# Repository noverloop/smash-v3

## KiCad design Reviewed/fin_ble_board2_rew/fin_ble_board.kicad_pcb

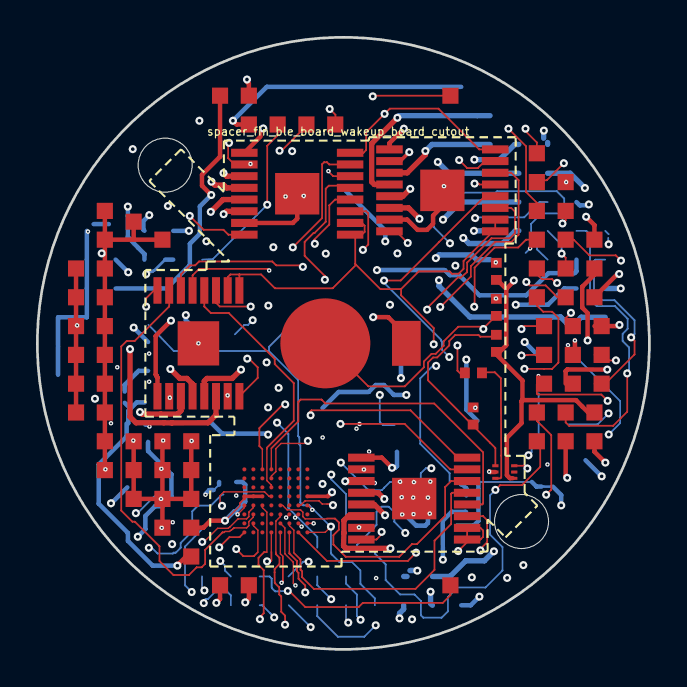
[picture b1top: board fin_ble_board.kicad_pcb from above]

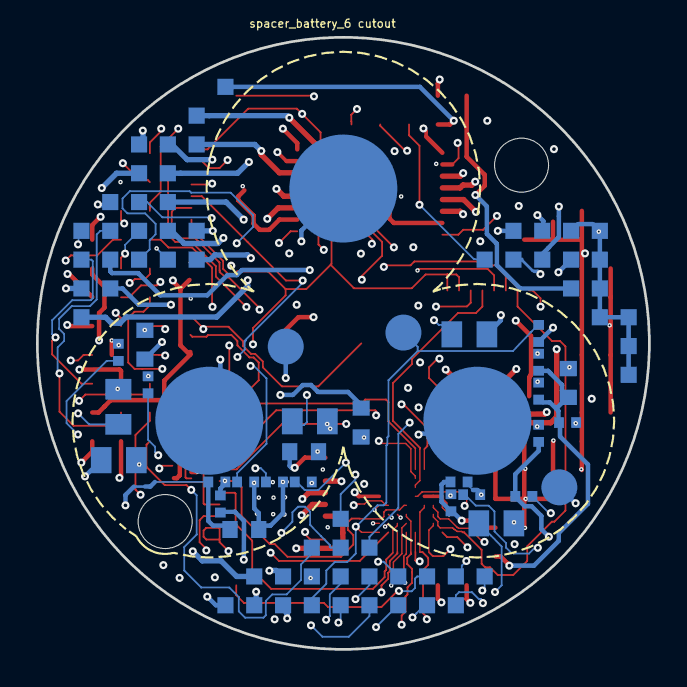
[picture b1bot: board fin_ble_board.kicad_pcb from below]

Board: 14 copper layers, 34.0 x 34.0 mm, 44 parts (31 on the bottom side), 81 nets.

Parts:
C_COMP_PZ: C0402 X7R 100nF; Capacitor_SMD_C_0402_1005Metric
C_FIN1_DVDD, C_FIN2_DVDD, C_FIN3_DVDD, C_FIN4_DVDD: C-Series MIL-PRF-32535 X7R 0805 1uF; Capacitor_SMD_C_0805_2012Metric
C_FIN1_VM, C_FIN2_VM, C_FIN3_VM, C_FIN4_VM: C0402 X7R 100nF; Capacitor_SMD_C_0402_1005Metric
C_FIN_VM_BULK_1, C_FIN_VM_BULK_2, C_FIN_VM_BULK_3, C_FIN_VM_BULK_4, C_FIN_VM_BULK_5: C-Series MIL-PRF-32535 X7R 0603 2.2uF; Capacitor_SMD_C_0603_1608Metric
C_FIN_VREF: C0402 X7R 100nF; Capacitor_SMD_C_0402_1005Metric
C_G0B1_FIN_BULK: C-Series MIL-PRF-32535 X7R 0805 1uF; Capacitor_SMD_C_0805_2012Metric
C_G0B1_FIN_NRST, C_G0B1_FIN_VDD1, C_G0B1_FIN_VDD2, C_G0B1_FIN_VREF: C0402 X7R 100nF; Capacitor_SMD_C_0402_1005Metric
C_J_HALL_FIN_VCC: C0402 X7R 100nF; Capacitor_SMD_C_0402_1005Metric
J_HALL_FIN_GND: J_HALL_FIN_GND; Pogo_Pad_D2.0mm
J_HALL_FIN_OUT: J_HALL_FIN_OUT; Pogo_Pad_D2.0mm
J_HALL_FIN_VCC: J_HALL_FIN_VCC; Pogo_Pad_D2.0mm
J_fin_ble_board_spacer_fin_ble_board_wakeup_board: LGA_lands; J_fin_ble_board_spacer_fin_ble_board_wakeup_board
P_CELL_CONTACTS: BatteryContacts_3
P_PIEZO: SMD10T04R111; PiezoDisc_SMD10T04R111
P_fin_ble_board_spacer_battery_6: LGA_lands; P_fin_ble_board_spacer_battery_6
R_COMP_SER: CRCW0402 100k 1% e3; Resistor_SMD_R_0402_1005Metric
R_FIN1_DECAY, R_FIN2_DECAY, R_FIN3_DECAY, R_FIN4_DECAY: CRCW0402 44.2k 1% e3; Resistor_SMD_R_0402_1005Metric
R_G0B1_FIN_NRST: CRCW0402 10k 1% e3; Resistor_SMD_R_0402_1005Metric
R_J_HALL_FIN_PU: CRCW0402 10k 1% e3; Resistor_SMD_R_0402_1005Metric
R_PIEZO_BLEED: CRCW0402 1M 1% e3; Resistor_SMD_R_0402_1005Metric
R_THR1: CRCW0402 1M 1% e3; Resistor_SMD_R_0402_1005Metric
R_THR2: CRCW0402 100k 1% e3; Resistor_SMD_R_0402_1005Metric
U_COMP_PZ: TLV3691IDPFR; DPF0006A
U_FIN1, U_FIN2, U_FIN3, U_FIN4: DRV8428EPWPR; SOP65P640X120-17N
U_G0B1_FIN: STM32G0B1REI6N; BGA64C50P8X8_500X500X60

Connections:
3V3: C_G0B1_FIN_BULK.1, C_G0B1_FIN_VDD1.1, C_G0B1_FIN_VDD2.1, C_G0B1_FIN_VREF.1, C_J_HALL_FIN_VCC.1, J_HALL_FIN_VCC.1, J_fin_ble_board_spacer_fin_ble_board_wa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.1, J_fin_ble_board_spacer_fin_ble_board_wa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.35, J_fin_ble_board_spacer_fin_ble_board_wa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.41, P_fin_ble_board_spacer_battery_6.23, P_fin_ble_board_spacer_battery_6.47, P_fin_ble_board_spacer_battery_6.52, R_G0B1_FIN_NRST.1, R_J_HALL_FIN_PU.1, U_G0B1_FIN.D1, U_G0B1_FIN.D2, U_G0B1_FIN.D3, U_G0B1_FIN.D8
3V3_AON: C_COMP_PZ.1, J_fin_ble_board_spacer_fin_ble_board_wa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.2, J_fin_ble_board_spacer_fin_ble_board_wa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.36, P_fin_ble_board_spacer_battery_6.24, P_fin_ble_board_spacer_battery_6.48, R_THR1.1, U_COMP_PZ.6
ACTIVATE_CONFIRM: J_fin_ble_board_spacer_fin_ble_board_wa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.3, P_fin_ble_board_spacer_battery_6.3
ACTIVATE_SET: J_fin_ble_board_spacer_fin_ble_board_wa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.4, P_fin_ble_board_spacer_battery_6.4
BAT_CELL1_POS: J_fin_ble_board_spacer_fin_ble_board_wa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.5, P_CELL_CONTACTS.1
BAT_CELL2_POS: J_fin_ble_board_spacer_fin_ble_board_wa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.6, P_CELL_CONTACTS.2
BAT_CELL3_POS: J_fin_ble_board_spacer_fin_ble_board_wa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.7, P_CELL_CONTACTS.3
BAT_PROT: J_fin_ble_board_spacer_fin_ble_board_wa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.8, J_fin_ble_board_spacer_fin_ble_board_wa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.37, P_fin_ble_board_spacer_battery_6.5, P_fin_ble_board_spacer_battery_6.49
BAT_RAW: J_fin_ble_board_spacer_fin_ble_board_wa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.9, J_fin_ble_board_spacer_fin_ble_board_wa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.38, P_fin_ble_board_spacer_battery_6.6, P_fin_ble_board_spacer_battery_6.50
BOOT0: J_fin_ble_board_spacer_fin_ble_board_wa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.10, P_fin_ble_board_spacer_battery_6.7
COMP_5V: J_fin_ble_board_spacer_fin_ble_board_wa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.11, J_fin_ble_board_spacer_fin_ble_board_wa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.39, P_fin_ble_board_spacer_battery_6.8, P_fin_ble_board_spacer_battery_6.51
COMP_5V_RAW: C_FIN1_VM.1, C_FIN2_VM.1, C_FIN3_VM.1, C_FIN4_VM.1, C_FIN_VM_BULK_1.1, C_FIN_VM_BULK_2.1, C_FIN_VM_BULK_3.1, C_FIN_VM_BULK_4.1, C_FIN_VM_BULK_5.1, J_fin_ble_board_spacer_fin_ble_board_wa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.12, J_fin_ble_board_spacer_fin_ble_board_wa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.40, U_FIN1.1, U_FIN2.1, U_FIN3.1, U_FIN4.1
COMP_INM: R_THR1.2, R_THR2.1, U_COMP_PZ.3
COMP_INP: R_COMP_SER.2, U_COMP_PZ.1
COMP_OUT: J_fin_ble_board_spacer_fin_ble_board_wa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.13, U_COMP_PZ.4
COMP_SWDCLK: J_fin_ble_board_spacer_fin_ble_board_wa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.14, P_fin_ble_board_spacer_battery_6.9
COMP_SWDIO: J_fin_ble_board_spacer_fin_ble_board_wa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.15, P_fin_ble_board_spacer_battery_6.10
EXT_CAN_RX: J_fin_ble_board_spacer_fin_ble_board_wa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.16, P_fin_ble_board_spacer_battery_6.11
EXT_CAN_TX: J_fin_ble_board_spacer_fin_ble_board_wa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.17, P_fin_ble_board_spacer_battery_6.14
FIN1_AEN: U_FIN1.15, U_G0B1_FIN.E3
FIN1_AOUT1: P_fin_ble_board_spacer_battery_6.13, U_FIN1.3
FIN1_AOUT2: P_fin_ble_board_spacer_battery_6.12, U_FIN1.4
FIN1_APH: U_FIN1.14, U_G0B1_FIN.H5
FIN1_BEN: U_FIN1.13, U_G0B1_FIN.F5
FIN1_BOUT1: P_fin_ble_board_spacer_battery_6.15, U_FIN1.6
FIN1_BOUT2: P_fin_ble_board_spacer_battery_6.16, U_FIN1.5
FIN1_BPH: U_FIN1.12, U_G0B1_FIN.B4
FIN1_DECAY: R_FIN1_DECAY.1, U_FIN1.11
FIN1_DVDD: C_FIN1_DVDD.1, U_FIN1.8
FIN2_AEN: U_FIN2.15, U_G0B1_FIN.F2
FIN2_AOUT1: P_fin_ble_board_spacer_battery_6.17, U_FIN2.3
FIN2_AOUT2: P_fin_ble_board_spacer_battery_6.18, U_FIN2.4
FIN2_APH: U_FIN2.14, U_G0B1_FIN.H6
FIN2_BEN: U_FIN2.13, U_G0B1_FIN.G5
FIN2_BOUT1: P_fin_ble_board_spacer_battery_6.19, U_FIN2.6
FIN2_BOUT2: P_fin_ble_board_spacer_battery_6.20, U_FIN2.5
FIN2_BPH: U_FIN2.12, U_G0B1_FIN.C4
FIN2_DECAY: R_FIN2_DECAY.1, U_FIN2.11
FIN2_DVDD: C_FIN2_DVDD.1, U_FIN2.8
FIN3_AEN: U_FIN3.15, U_G0B1_FIN.G2
FIN3_AOUT1: P_fin_ble_board_spacer_battery_6.21, U_FIN3.3
FIN3_AOUT2: P_fin_ble_board_spacer_battery_6.22, U_FIN3.4
FIN3_APH: U_FIN3.14, U_G0B1_FIN.E7
FIN3_BEN: U_FIN3.13, U_G0B1_FIN.H7
FIN3_BOUT1: P_fin_ble_board_spacer_battery_6.1, U_FIN3.6
FIN3_BOUT2: P_fin_ble_board_spacer_battery_6.2, U_FIN3.5
FIN3_BPH: U_FIN3.12, U_G0B1_FIN.D4
FIN3_DECAY: R_FIN3_DECAY.1, U_FIN3.11
FIN3_DVDD: C_FIN3_DVDD.1, U_FIN3.8
FIN4_AEN: U_FIN4.15, U_G0B1_FIN.H1
FIN4_AOUT1: P_fin_ble_board_spacer_battery_6.25, U_FIN4.3
FIN4_AOUT2: P_fin_ble_board_spacer_battery_6.26, U_FIN4.4
FIN4_APH: U_FIN4.14, U_G0B1_FIN.E5
FIN4_BEN: U_FIN4.13, U_G0B1_FIN.G6
FIN4_BOUT1: P_fin_ble_board_spacer_battery_6.27, U_FIN4.6
FIN4_BOUT2: P_fin_ble_board_spacer_battery_6.28, U_FIN4.5
FIN4_BPH: U_FIN4.12, U_G0B1_FIN.A4
FIN4_DECAY: R_FIN4_DECAY.1, U_FIN4.11
FIN4_DVDD: C_FIN4_DVDD.1, U_FIN4.8
FIN_HALL: J_HALL_FIN_OUT.1, P_fin_ble_board_spacer_battery_6.29, R_J_HALL_FIN_PU.2, U_G0B1_FIN.H8
FIN_NSLEEP: U_FIN1.16, U_FIN2.16, U_FIN3.16, U_FIN4.16, U_G0B1_FIN.A3
FIN_VREF: C_FIN_VREF.1, U_FIN1.9, U_FIN1.10, U_FIN2.9, U_FIN2.10, U_FIN3.9, U_FIN3.10, U_FIN4.9, U_FIN4.10, U_G0B1_FIN.H4
FLEX_GND: C_COMP_PZ.2, C_FIN1_DVDD.2, C_FIN1_VM.2, C_FIN2_DVDD.2, C_FIN2_VM.2, C_FIN3_DVDD.2, C_FIN3_VM.2, C_FIN4_DVDD.2, C_FIN4_VM.2, C_FIN_VM_BULK_1.2, C_FIN_VM_BULK_2.2, C_FIN_VM_BULK_3.2, C_FIN_VM_BULK_4.2, C_FIN_VM_BULK_5.2, C_FIN_VREF.2, C_G0B1_FIN_BULK.2, C_G0B1_FIN_NRST.2, C_G0B1_FIN_VDD1.2, C_G0B1_FIN_VDD2.2, C_G0B1_FIN_VREF.2, C_J_HALL_FIN_VCC.2, J_HALL_FIN_GND.1, J_fin_ble_board_spacer_fin_ble_board_wa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.18, J_fin_ble_board_spacer_fin_ble_board_wa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.42, J_fin_ble_board_spacer_fin_ble_board_wa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.43, J_fin_ble_board_spacer_fin_ble_board_wa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.44, J_fin_ble_board_spacer_fin_ble_board_wa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.45, J_fin_ble_board_spacer_fin_ble_board_wa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.46, J_fin_ble_board_spacer_fin_ble_board_wa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.47, J_fin_ble_board_spacer_fin_ble_board_wa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.48, J_fin_ble_board_spacer_fin_ble_board_wa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.49, J_fin_ble_board_spacer_fin_ble_board_wa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.50, J_fin_ble_board_spacer_fin_ble_board_wa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.51, J_fin_ble_board_spacer_fin_ble_board_wa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.52, J_fin_ble_board_spacer_fin_ble_board_wa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.53, J_fin_ble_board_spacer_fin_ble_board_wa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.54, J_fin_ble_board_spacer_fin_ble_board_wa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.55, J_fin_ble_board_spacer_fin_ble_board_wa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.56, J_fin_ble_board_spacer_fin_ble_board_wa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.57, J_fin_ble_board_spacer_fin_ble_board_wa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.58, J_fin_ble_board_spacer_fin_ble_board_wa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.59, J_fin_ble_board_spacer_fin_ble_board_wa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.60, J_fin_ble_board_spacer_fin_ble_board_wa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.61, J_fin_ble_board_spacer_fin_ble_board_wa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.62, J_fin_ble_board_spacer_fin_ble_board_wa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.63, J_fin_ble_board_spacer_fin_ble_board_wa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.64, J_fin_ble_board_spacer_fin_ble_board_wa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.65, J_fin_ble_board_spacer_fin_ble_board_wa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.66, J_fin_ble_board_spacer_fin_ble_board_wa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.67, J_fin_ble_board_spacer_fin_ble_board_wa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.68, J_fin_ble_board_spacer_fin_ble_board_wa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.69, P_PIEZO.2, P_fin_ble_board_spacer_battery_6.30, P_fin_ble_board_spacer_battery_6.53, P_fin_ble_board_spacer_battery_6.54, P_fin_ble_board_spacer_battery_6.55, P_fin_ble_board_spacer_battery_6.56, P_fin_ble_board_spacer_battery_6.57, P_fin_ble_board_spacer_battery_6.58, P_fin_ble_board_spacer_battery_6.59, P_fin_ble_board_spacer_battery_6.60, R_FIN1_DECAY.2, R_FIN2_DECAY.2, R_FIN3_DECAY.2, R_FIN4_DECAY.2, R_PIEZO_BLEED.2, R_THR2.2, U_COMP_PZ.2, U_FIN1.2, U_FIN1.7, U_FIN1.17, U_FIN2.2, U_FIN2.7, U_FIN2.17, U_FIN3.2, U_FIN3.7, U_FIN3.17, U_FIN4.2, U_FIN4.7, U_FIN4.17, U_G0B1_FIN.E1, U_G0B1_FIN.E8
G0B1_FIN_NRST: C_G0B1_FIN_NRST.1, R_G0B1_FIN_NRST.2, U_G0B1_FIN.E2
GPIO_EXT_0: J_fin_ble_board_spacer_fin_ble_board_wa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.19, P_fin_ble_board_spacer_battery_6.31
GPIO_EXT_1: J_fin_ble_board_spacer_fin_ble_board_wa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.20, P_fin_ble_board_spacer_battery_6.32
GPIO_EXT_2: J_fin_ble_board_spacer_fin_ble_board_wa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.21, P_fin_ble_board_spacer_battery_6.33
GPIO_EXT_3: J_fin_ble_board_spacer_fin_ble_board_wa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.22, P_fin_ble_board_spacer_battery_6.34
H3LIS_INT1: J_fin_ble_board_spacer_fin_ble_board_wa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.23, P_fin_ble_board_spacer_battery_6.35
I2C3_SCL: J_fin_ble_board_spacer_fin_ble_board_wa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.24, P_fin_ble_board_spacer_battery_6.36
I2C3_SDA: J_fin_ble_board_spacer_fin_ble_board_wa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.25, P_fin_ble_board_spacer_battery_6.37
JUMP_WAKE: J_fin_ble_board_spacer_fin_ble_board_wa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.26, P_fin_ble_board_spacer_battery_6.38
NRST: J_fin_ble_board_spacer_fin_ble_board_wa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.27, P_fin_ble_board_spacer_battery_6.39
PIEZO_P: P_PIEZO.1, R_COMP_SER.1, R_PIEZO_BLEED.1
SWO: J_fin_ble_board_spacer_fin_ble_board_wa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.28, P_fin_ble_board_spacer_battery_6.40
SYS_I2C_SCL: J_fin_ble_board_spacer_fin_ble_board_wa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.29, P_fin_ble_board_spacer_battery_6.41
SYS_I2C_SDA: J_fin_ble_board_spacer_fin_ble_board_wa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.30, P_fin_ble_board_spacer_battery_6.42
SYS_SPI_CS_FIN: J_fin_ble_board_spacer_fin_ble_board_wa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.31, P_fin_ble_board_spacer_battery_6.43, U_G0B1_FIN.G7
SYS_SPI_MISO: J_fin_ble_board_spacer_fin_ble_board_wa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.32, P_fin_ble_board_spacer_battery_6.44, U_G0B1_FIN.F6
SYS_SPI_MOSI: J_fin_ble_board_spacer_fin_ble_board_wa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.33, P_fin_ble_board_spacer_battery_6.45, U_G0B1_FIN.F7
SYS_SPI_SCLK: J_fin_ble_board_spacer_fin_ble_board_wa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.34, P_fin_ble_board_spacer_battery_6.46, U_G0B1_FIN.G8

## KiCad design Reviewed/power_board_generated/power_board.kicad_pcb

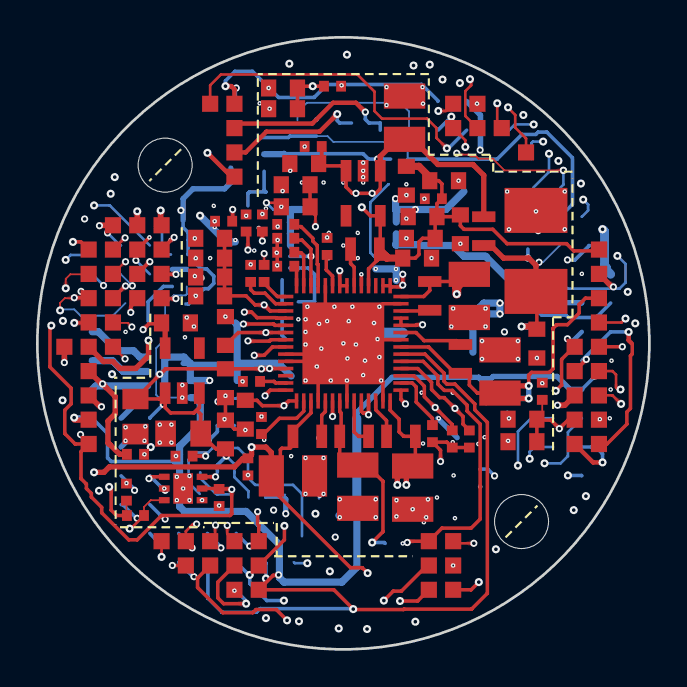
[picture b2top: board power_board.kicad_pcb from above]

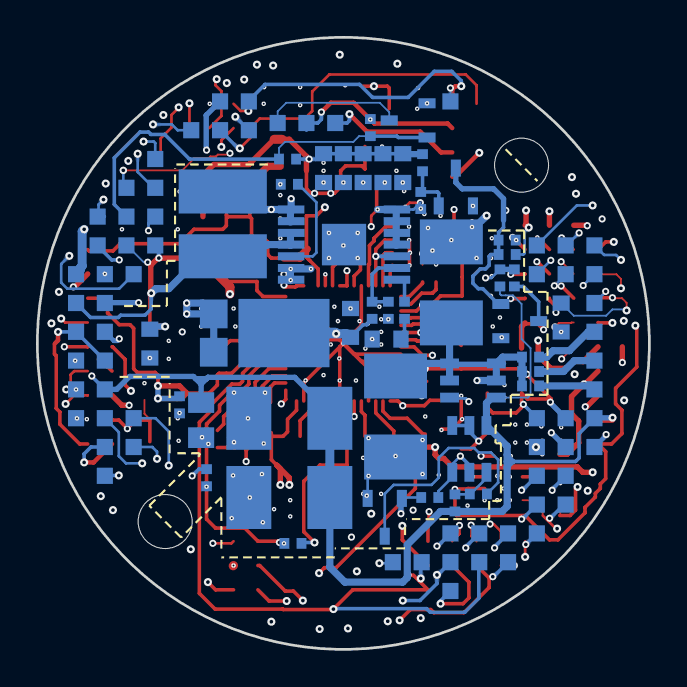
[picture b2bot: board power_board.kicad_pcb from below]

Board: 8 copper layers, 34.0 x 34.0 mm, 114 parts (45 on the bottom side), 98 nets.

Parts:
CBAT1, CBAT2: T528W 100uF (7343-15 thinnest variant); Capacitor_Tantalum_SMD_CP_EIA-7343-15_Kemet-W
CBAT3: C-Series MIL-PRF-32535 X7R 0805 1uF; Capacitor_SMD_C_0805_2012Metric
C_BAT_BULK1, C_BAT_BULK2: T528W 470uF (7343-15 thinnest variant); Capacitor_Tantalum_SMD_CP_EIA-7343-15_Kemet-W
C_BOOST_COMP: C-Series MIL-PRF-32535 X7R 0603 220nF; Capacitor_SMD_C_0603_1608Metric
C_BOOST_OUT1: T528W 47uF (7343-15 thinnest variant); Capacitor_Tantalum_SMD_CP_EIA-7343-15_Kemet-W
C_BOOST_OUT2_1, C_BOOST_OUT2_2, C_BOOST_OUT2_3, C_BOOST_OUT2_4, C_BOOST_OUT2_5: C-Series MIL-PRF-32535 X7R 0603 2.2uF; Capacitor_SMD_C_0603_1608Metric
C_BOOST_OUT3: C0402 X7R 100nF; Capacitor_SMD_C_0402_1005Metric
C_BOOST_SS: C0402 X7R 47nF; Capacitor_SMD_C_0402_1005Metric
C_CAM_LDO_VAA_IN: C-Series MIL-PRF-32535 X7R 0805 1uF; Capacitor_SMD_C_0805_2012Metric
C_CAM_LDO_VAA_OUT_1, C_CAM_LDO_VAA_OUT_2: C-Series MIL-PRF-32535 X7R 0603 2.2uF; Capacitor_SMD_C_0603_1608Metric
C_CAM_LDO_VDD_IN: C-Series MIL-PRF-32535 X7R 0805 1uF; Capacitor_SMD_C_0805_2012Metric
C_CAM_LDO_VDD_OUT: C-Series MIL-PRF-32535 X7R 0603 2.2uF; Capacitor_SMD_C_0603_1608Metric
C_PMIC_0V9_1, C_PMIC_0V82_1, C_PMIC_1V8_1, C_PMIC_3V3_1: T491T 22uF (3528-12 thinnest variant); Capacitor_Tantalum_SMD_CP_EIA-3528-12_Kemet-T
C_PMIC_0V9_2, C_PMIC_0V82_2, C_PMIC_1V2_2, C_PMIC_1V8_2, C_PMIC_2V8_2, C_PMIC_3V3_2: C0402 X7R 100nF; Capacitor_SMD_C_0402_1005Metric
C_PMIC_1V2_1_1, C_PMIC_1V2_1_2, C_PMIC_1V2_1_3, C_PMIC_1V2_1_4, C_PMIC_1V2_1_5, C_PMIC_2V8_1_1, C_PMIC_2V8_1_2, C_PMIC_5V_FILT_1, C_PMIC_5V_FILT_2, C_PMIC_5V_FILT_3, C_PMIC_5V_FILT_4, C_PMIC_5V_FILT_5: C-Series MIL-PRF-32535 X7R 0603 2.2uF; Capacitor_SMD_C_0603_1608Metric
C_PMIC_INTLDO_1, C_PMIC_INTLDO_2: C-Series MIL-PRF-32535 X7R 0603 2.2uF; Capacitor_SMD_C_0603_1608Metric
C_PMIC_LDO1, C_PMIC_LDO2, C_PMIC_LDO4, C_PMIC_LDO6, C_PMIC_LDO7, C_PMIC_LDO8: C0402 X7R 100nF; Capacitor_SMD_C_0402_1005Metric
C_PMIC_VIN1: T491T 22uF (3528-12 thinnest variant); Capacitor_Tantalum_SMD_CP_EIA-3528-12_Kemet-T
C_PMIC_VIN2: C0402 X7R 100nF; Capacitor_SMD_C_0402_1005Metric
C_PMIC_VIN3, C_PMIC_VIN4, C_PMIC_VIN5, C_PMIC_VIN6: C-Series MIL-PRF-32535 X7R 0603 2.2uF; Capacitor_SMD_C_0603_1608Metric
C_PMIC_VLX7: C0402 X7R 100nF; Capacitor_SMD_C_0402_1005Metric
C_PMIC_VOUT7: C0402 X7R 100nF; Capacitor_SMD_C_0402_1005Metric
C_PMIC_VPP_1: T491T 22uF (3528-12 thinnest variant); Capacitor_Tantalum_SMD_CP_EIA-3528-12_Kemet-T
C_PMIC_VPP_2: C0402 X7R 100nF; Capacitor_SMD_C_0402_1005Metric
C_TMP1: C0402 X7R 100nF; Capacitor_SMD_C_0402_1005Metric
C_USB_VBUS_1, C_USB_VBUS_2, C_USB_VBUS_3, C_USB_VBUS_4, C_USB_VBUS_5: C-Series MIL-PRF-32535 X7R 0603 2.2uF; Capacitor_SMD_C_0603_1608Metric
D_BOOST_COMP: PMEG040V050EPE-QZ; PMEG040V050EPEQZ
J_power_board_spacer_power_board_companion_compute: LGA_lands; J_power_board_spacer_power_board_companion_compute
L_BOOST_COMP: 744043100; INDPM4848X280N
L_PMIC_BUCK1, L_PMIC_BUCK5, L_PMIC_BUCK6: TMS201210ALM-1R0MTAA; Inductor_SMD_L_2012_2.0x1.25mm
L_PMIC_BUCK2, L_PMIC_BUCK3, L_PMIC_BUCK4: TMS201210ALM-2R2MTAA; Inductor_SMD_L_2012_2.0x1.25mm
L_PMIC_FILT: TMS201210ALM-1R0MTAA; Inductor_SMD_L_2012_2.0x1.25mm
P_power_board_spacer_wakeup_board_power_board: LGA_lands; P_power_board_spacer_wakeup_board_power_board
Q_ISO: DMP6110SVT-7; SOT95P280X100-6N
Q_ISO_DRV: BSS138LT1G; SOT96P237X111-3N
Q_ISO_USB: BSS138LT1G; SOT96P237X111-3N
Q_USBOR_DRV: BSS138LT1G; SOT96P237X111-3N
Q_USB_OR: DMP6110SVT-7; SOT95P280X100-6N
Q_USB_WAKE: BSS138LT1G; SOT96P237X111-3N
R_BAT1_ISO, R_BAT2_ISO, R_BAT3_ISO: CRCW0402 200m 1% e3; Resistor_SMD_R_0402_1005Metric
R_BOOST_COMP: CRCW0402 1.6k 1% e3; Resistor_SMD_R_0402_1005Metric
R_BOOST_FREQ: CRCW0402 176k 1% e3; Resistor_SMD_R_0402_1005Metric
R_BOOST_R1: CRCW0402 309k 1% e3; Resistor_SMD_R_0402_1005Metric
R_BOOST_R2: CRCW0402 100k 1% e3; Resistor_SMD_R_0402_1005Metric
R_ISO_EN_PD: CRCW0402 100k 1% e3; Resistor_SMD_R_0402_1005Metric
R_ISO_EN_S: CRCW0402 10k 1% e3; Resistor_SMD_R_0402_1005Metric
R_ISO_H: CRCW0402 100k 1% e3; Resistor_SMD_R_0402_1005Metric
R_ISO_L: CRCW0402 10k 1% e3; Resistor_SMD_R_0402_1005Metric
R_ISO_USB_H: CRCW0402 100k 1% e3; Resistor_SMD_R_0402_1005Metric
R_ISO_USB_L: CRCW0402 100k 1% e3; Resistor_SMD_R_0402_1005Metric
R_PMIC_NRST: CRCW0402 10k 1% e3; Resistor_SMD_R_0402_1005Metric
R_PMIC_PONKEY: CRCW0402 10k 1% e3; Resistor_SMD_R_0402_1005Metric
R_PMIC_PWRCTRL1_PD, R_PMIC_PWRCTRL2_PD, R_PMIC_PWRCTRL3_PD: CRCW0402 10k 1% e3; Resistor_SMD_R_0402_1005Metric
R_PMIC_PWR_OK: CRCW0402 10k 1% e3; Resistor_SMD_R_0402_1005Metric
R_PMIC_WAKEUP: CRCW0402 10k 1% e3; Resistor_SMD_R_0402_1005Metric
R_TMP1_ALERT_PU: CRCW0402 10k 1% e3; Resistor_SMD_R_0402_1005Metric
R_USBOR_H: CRCW0402 100k 1% e3; Resistor_SMD_R_0402_1005Metric
R_USBOR_L: CRCW0402 10k 1% e3; Resistor_SMD_R_0402_1005Metric
R_USBOR_USB_H: CRCW0402 100k 1% e3; Resistor_SMD_R_0402_1005Metric
R_USBOR_USB_L: CRCW0402 100k 1% e3; Resistor_SMD_R_0402_1005Metric
R_USBWK_G: CRCW0402 10k 1% e3; Resistor_SMD_R_0402_1005Metric
R_USBWK_PD: CRCW0402 100k 1% e3; Resistor_SMD_R_0402_1005Metric
U_CAM_LDO_VAA: LP5907MFX-2.8/NOPB; SOT95P280X145-5N
U_CAM_LDO_VDD: LP5907MFX-1.2/NOPB; SOT95P280X145-5N
U_COMP_BOOST: TPS61175PWPR; SOP65P640X120-15N
U_PMIC: STPMIC25APQR; QFN40P650X650X90-57N-D
U_TMP1: TMP117MAIDRVR; SON65P200X200X80-7N

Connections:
3V3: C_TMP1.1, J_power_board_spacer_power_board_compan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.1, J_power_board_spacer_power_board_compan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.57, P_power_board_spacer_wakeup_board_power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.1, P_power_board_spacer_wakeup_board_power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.55, P_power_board_spacer_wakeup_board_power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.62, R_PMIC_NRST.1, R_PMIC_PONKEY.1, R_PMIC_PWR_OK.1, R_PMIC_WAKEUP.1, U_PMIC.29, U_TMP1.5
ACTIVATE_CONFIRM: J_power_board_spacer_power_board_compan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.2, P_power_board_spacer_wakeup_board_power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.2
ACTIVATE_SET: J_power_board_spacer_power_board_compan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.3, P_power_board_spacer_wakeup_board_power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.3
BAT_CELL1_POS: P_power_board_spacer_wakeup_board_power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.4, R_BAT1_ISO.1
BAT_CELL2_POS: P_power_board_spacer_wakeup_board_power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.5, R_BAT2_ISO.1
BAT_CELL3_POS: P_power_board_spacer_wakeup_board_power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.6, R_BAT3_ISO.1
BAT_ISO_DRIVE: J_power_board_spacer_power_board_compan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.4, R_ISO_EN_S.1
BAT_ISO_EN: Q_ISO_DRV.1, Q_ISO_USB.3, R_ISO_EN_PD.1, R_ISO_EN_S.2
BAT_ISO_G: Q_ISO.3, R_ISO_H.2, R_ISO_L.1
BAT_ISO_GD: Q_ISO_DRV.3, R_ISO_L.2
BAT_ISO_USBG: Q_ISO_USB.1, R_ISO_USB_H.2, R_ISO_USB_L.1
BAT_PROT: CBAT1.1, CBAT2.1, CBAT3.1, J_power_board_spacer_power_board_compan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.5, J_power_board_spacer_power_board_compan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.58, P_power_board_spacer_wakeup_board_power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.7, P_power_board_spacer_wakeup_board_power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.56, Q_ISO.4, Q_USB_OR.4, R_ISO_H.1, R_USBOR_H.1
BAT_RAW: C_BAT_BULK1.1, C_BAT_BULK2.1, P_power_board_spacer_wakeup_board_power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.8, P_power_board_spacer_wakeup_board_power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.57, Q_ISO.1, Q_ISO.2, Q_ISO.5, Q_ISO.6, R_BAT1_ISO.2, R_BAT2_ISO.2, R_BAT3_ISO.2
BOOT0: J_power_board_spacer_power_board_compan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.6, P_power_board_spacer_wakeup_board_power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.9
COMP_0V9: C_PMIC_0V9_1.1, C_PMIC_0V9_2.1, J_power_board_spacer_power_board_compan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.8, J_power_board_spacer_power_board_compan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.60, L_PMIC_BUCK1.2, U_PMIC.42
COMP_0V82: C_PMIC_0V82_1.1, C_PMIC_0V82_2.1, J_power_board_spacer_power_board_compan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.7, J_power_board_spacer_power_board_compan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.59, L_PMIC_BUCK5.2, U_PMIC.35
COMP_1V2: C_CAM_LDO_VDD_OUT.1, C_PMIC_1V2_1_1.1, C_PMIC_1V2_1_2.1, C_PMIC_1V2_1_3.1, C_PMIC_1V2_1_4.1, C_PMIC_1V2_1_5.1, C_PMIC_1V2_2.1, J_power_board_spacer_power_board_compan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.9, J_power_board_spacer_power_board_compan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.61, L_PMIC_BUCK6.2, U_CAM_LDO_VDD.5, U_PMIC.46
COMP_1V8: C_PMIC_1V8_1.1, C_PMIC_1V8_2.1, J_power_board_spacer_power_board_compan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.10, J_power_board_spacer_power_board_compan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.62, L_PMIC_BUCK4.2, P_power_board_spacer_wakeup_board_power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.10, P_power_board_spacer_wakeup_board_power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.58, U_PMIC.17
COMP_2V8: C_CAM_LDO_VAA_OUT_1.1, C_CAM_LDO_VAA_OUT_2.1, C_PMIC_2V8_1_1.1, C_PMIC_2V8_1_2.1, C_PMIC_2V8_2.1, J_power_board_spacer_power_board_compan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.11, J_power_board_spacer_power_board_compan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.63, U_CAM_LDO_VAA.5, U_PMIC.7
COMP_3V3: C_PMIC_3V3_1.1, C_PMIC_3V3_2.1, J_power_board_spacer_power_board_compan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.12, J_power_board_spacer_power_board_compan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.64, L_PMIC_BUCK2.2, R_TMP1_ALERT_PU.1, U_PMIC.28
COMP_5V: C_CAM_LDO_VAA_IN.1, C_CAM_LDO_VDD_IN.1, C_PMIC_5V_FILT_1.1, C_PMIC_5V_FILT_2.1, C_PMIC_5V_FILT_3.1, C_PMIC_5V_FILT_4.1, C_PMIC_5V_FILT_5.1, C_PMIC_VIN1.1, C_PMIC_VIN2.1, C_PMIC_VIN3.1, C_PMIC_VIN4.1, C_PMIC_VIN5.1, C_PMIC_VIN6.1, J_power_board_spacer_power_board_compan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.13, J_power_board_spacer_power_board_compan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.65, L_PMIC_FILT.2, P_power_board_spacer_wakeup_board_power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.11, P_power_board_spacer_wakeup_board_power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.59, U_CAM_LDO_VAA.1, U_CAM_LDO_VAA.3, U_CAM_LDO_VDD.1, U_CAM_LDO_VDD.3, U_PMIC.3, U_PMIC.6, U_PMIC.11, U_PMIC.15, U_PMIC.20, U_PMIC.24, U_PMIC.25, U_PMIC.38, U_PMIC.39, U_PMIC.43, U_PMIC.44, U_PMIC.49, U_PMIC.50
COMP_5V_COMP: R_BOOST_COMP.1, U_COMP_BOOST.8
COMP_5V_COMP_C: C_BOOST_COMP.1, R_BOOST_COMP.2
COMP_5V_FB: R_BOOST_R1.2, R_BOOST_R2.1, U_COMP_BOOST.9
COMP_5V_FREQ: R_BOOST_FREQ.1, U_COMP_BOOST.10
COMP_5V_RAW: C_BOOST_OUT1.1, C_BOOST_OUT2_1.1, C_BOOST_OUT2_2.1, C_BOOST_OUT2_3.1, C_BOOST_OUT2_4.1, C_BOOST_OUT2_5.1, C_BOOST_OUT3.1, D_BOOST_COMP.3, L_PMIC_FILT.1, P_power_board_spacer_wakeup_board_power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.12, P_power_board_spacer_wakeup_board_power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.60, R_BOOST_R1.1
COMP_5V_SS: C_BOOST_SS.1, U_COMP_BOOST.5
COMP_5V_SW: D_BOOST_COMP.1, D_BOOST_COMP.2, L_BOOST_COMP.2, U_COMP_BOOST.1, U_COMP_BOOST.2
COMP_OUT: J_power_board_spacer_power_board_compan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.14, P_power_board_spacer_wakeup_board_power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.13
COMP_SWDCLK: J_power_board_spacer_power_board_compan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.15, P_power_board_spacer_wakeup_board_power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.14
COMP_SWDIO: J_power_board_spacer_power_board_compan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.16, P_power_board_spacer_wakeup_board_power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.15
COMP_VPP: C_PMIC_VPP_1.1, C_PMIC_VPP_2.1, J_power_board_spacer_power_board_compan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.17, J_power_board_spacer_power_board_compan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.66, L_PMIC_BUCK3.2, U_PMIC.21
EXT_CAN_RX: J_power_board_spacer_power_board_compan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.18, P_power_board_spacer_wakeup_board_power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.16
EXT_CAN_TX: J_power_board_spacer_power_board_compan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.19, P_power_board_spacer_wakeup_board_power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.17
FLEX_GND: CBAT1.2, CBAT2.2, CBAT3.2, C_BAT_BULK1.2, C_BAT_BULK2.2, C_BOOST_COMP.2, C_BOOST_OUT1.2, C_BOOST_OUT2_1.2, C_BOOST_OUT2_2.2, C_BOOST_OUT2_3.2, C_BOOST_OUT2_4.2, C_BOOST_OUT2_5.2, C_BOOST_OUT3.2, C_BOOST_SS.2, C_CAM_LDO_VAA_IN.2, C_CAM_LDO_VAA_OUT_1.2, C_CAM_LDO_VAA_OUT_2.2, C_CAM_LDO_VDD_IN.2, C_CAM_LDO_VDD_OUT.2, C_PMIC_0V9_1.2, C_PMIC_0V9_2.2, C_PMIC_0V82_1.2, C_PMIC_0V82_2.2, C_PMIC_1V2_1_1.2, C_PMIC_1V2_1_2.2, C_PMIC_1V2_1_3.2, C_PMIC_1V2_1_4.2, C_PMIC_1V2_1_5.2, C_PMIC_1V2_2.2, C_PMIC_1V8_1.2, C_PMIC_1V8_2.2, C_PMIC_2V8_1_1.2, C_PMIC_2V8_1_2.2, C_PMIC_2V8_2.2, C_PMIC_3V3_1.2, C_PMIC_3V3_2.2, C_PMIC_5V_FILT_1.2, C_PMIC_5V_FILT_2.2, C_PMIC_5V_FILT_3.2, C_PMIC_5V_FILT_4.2, C_PMIC_5V_FILT_5.2, C_PMIC_INTLDO_1.2, C_PMIC_INTLDO_2.2, C_PMIC_LDO1.2, C_PMIC_LDO2.2, C_PMIC_LDO4.2, C_PMIC_LDO6.2, C_PMIC_LDO7.2, C_PMIC_LDO8.2, C_PMIC_VIN1.2, C_PMIC_VIN2.2, C_PMIC_VIN3.2, C_PMIC_VIN4.2, C_PMIC_VIN5.2, C_PMIC_VIN6.2, C_PMIC_VLX7.2, C_PMIC_VOUT7.2, C_PMIC_VPP_1.2, C_PMIC_VPP_2.2, C_TMP1.2, C_USB_VBUS_1.2, C_USB_VBUS_2.2, C_USB_VBUS_3.2, C_USB_VBUS_4.2, C_USB_VBUS_5.2, J_power_board_spacer_power_board_compan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.20, P_power_board_spacer_wakeup_board_power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.18, P_power_board_spacer_wakeup_board_power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.63, P_power_board_spacer_wakeup_board_power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.64, P_power_board_spacer_wakeup_board_power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.65, Q_ISO_DRV.2, Q_ISO_USB.2, Q_USBOR_DRV.2, Q_USB_WAKE.2, R_BOOST_FREQ.2, R_BOOST_R2.2, R_ISO_EN_PD.2, R_ISO_USB_L.2, R_PMIC_PWRCTRL1_PD.2, R_PMIC_PWRCTRL2_PD.2, R_PMIC_PWRCTRL3_PD.2, R_USBOR_USB_L.2, R_USBWK_PD.2, U_CAM_LDO_VAA.2, U_CAM_LDO_VDD.2, U_COMP_BOOST.6, U_COMP_BOOST.7, U_COMP_BOOST.11, U_COMP_BOOST.12, U_COMP_BOOST.13, U_COMP_BOOST.14, U_COMP_BOOST.15, U_PMIC.9, U_PMIC.10, U_PMIC.18, U_PMIC.22, U_PMIC.27, U_PMIC.36, U_PMIC.41, U_PMIC.47, U_PMIC.52, U_PMIC.57, U_TMP1.2, U_TMP1.4, U_TMP1.7
GPIO_EXT_0: J_power_board_spacer_power_board_compan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.21, P_power_board_spacer_wakeup_board_power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.19
GPIO_EXT_1: J_power_board_spacer_power_board_compan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.22, P_power_board_spacer_wakeup_board_power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.20
GPIO_EXT_2: J_power_board_spacer_power_board_compan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.23, P_power_board_spacer_wakeup_board_power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.21
GPIO_EXT_3: J_power_board_spacer_power_board_compan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.24, P_power_board_spacer_wakeup_board_power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.22
H3LIS_INT1: J_power_board_spacer_power_board_compan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.25, P_power_board_spacer_wakeup_board_power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.23
I2C2_SCL: J_power_board_spacer_power_board_compan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.26, P_power_board_spacer_wakeup_board_power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.24, U_PMIC.33, U_TMP1.1
I2C2_SDA: J_power_board_spacer_power_board_compan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.27, P_power_board_spacer_wakeup_board_power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.25, U_PMIC.34, U_TMP1.6
I2C3_SCL: J_power_board_spacer_power_board_compan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.28, P_power_board_spacer_wakeup_board_power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.26
I2C3_SDA: J_power_board_spacer_power_board_compan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.29, P_power_board_spacer_wakeup_board_power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.27
IMU1_INT: J_power_board_spacer_power_board_compan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.30, P_power_board_spacer_wakeup_board_power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.28
IMU2_INT: J_power_board_spacer_power_board_compan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.31, P_power_board_spacer_wakeup_board_power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.29
IMU3_INT: J_power_board_spacer_power_board_compan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.32, P_power_board_spacer_wakeup_board_power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.30
IR_TX: J_power_board_spacer_power_board_compan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.33, P_power_board_spacer_wakeup_board_power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.31
IR_WAKE: J_power_board_spacer_power_board_compan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.34, P_power_board_spacer_wakeup_board_power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.32
MAG_DRDY: J_power_board_spacer_power_board_compan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.35, P_power_board_spacer_wakeup_board_power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.33
MAIN_SW_GATE: P_power_board_spacer_wakeup_board_power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.34, Q_USB_WAKE.3
NRST: J_power_board_spacer_power_board_compan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.36, P_power_board_spacer_wakeup_board_power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.35
PMIC_INTLDO: C_PMIC_INTLDO_1.1, C_PMIC_INTLDO_2.1, U_PMIC.8
PMIC_LDO1_TERM: C_PMIC_LDO1.1, U_PMIC.14
PMIC_LDO2_TERM: C_PMIC_LDO2.1, U_PMIC.16
PMIC_LDO4_TERM: C_PMIC_LDO4.1, U_PMIC.13
PMIC_LDO6_TERM: C_PMIC_LDO6.1, U_PMIC.5
PMIC_LDO7_TERM: C_PMIC_LDO7.1, U_PMIC.4
PMIC_LDO8_TERM: C_PMIC_LDO8.1, U_PMIC.2
PMIC_NRST: R_PMIC_NRST.2, U_PMIC.31
PMIC_PONKEY: R_PMIC_PONKEY.2, U_PMIC.1
PMIC_PWRCTRL1: R_PMIC_PWRCTRL1_PD.1, U_PMIC.56
PMIC_PWRCTRL2: R_PMIC_PWRCTRL2_PD.1, U_PMIC.55
PMIC_PWRCTRL3: R_PMIC_PWRCTRL3_PD.1, U_PMIC.54
PMIC_PWR_OK: J_power_board_spacer_power_board_compan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.37, R_PMIC_PWR_OK.2, U_PMIC.32
PMIC_SW1: L_PMIC_BUCK1.1, U_PMIC.40
PMIC_SW2: L_PMIC_BUCK2.1, U_PMIC.26
PMIC_SW3: L_PMIC_BUCK3.1, U_PMIC.23
PMIC_SW4: L_PMIC_BUCK4.1, U_PMIC.19
PMIC_SW5: L_PMIC_BUCK5.1, U_PMIC.37
PMIC_SW6: L_PMIC_BUCK6.1, U_PMIC.48
PMIC_VLX7_TERM: C_PMIC_VLX7.1, U_PMIC.51
PMIC_VOUT7_TERM: C_PMIC_VOUT7.1, U_PMIC.53
PMIC_WAKEUP: R_PMIC_WAKEUP.2, U_PMIC.30
PWR_HOLD: J_power_board_spacer_power_board_compan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.38, P_power_board_spacer_wakeup_board_power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.36
REG_IN_MAIN: L_BOOST_COMP.1, P_power_board_spacer_wakeup_board_power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.37, P_power_board_spacer_wakeup_board_power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.61, U_COMP_BOOST.3, U_COMP_BOOST.4
SWO: J_power_board_spacer_power_board_compan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.39, P_power_board_spacer_wakeup_board_power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.38
SYS_I2C_SCL: J_power_board_spacer_power_board_compan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.40, P_power_board_spacer_wakeup_board_power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.39
SYS_I2C_SDA: J_power_board_spacer_power_board_compan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.41, P_power_board_spacer_wakeup_board_power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.40
SYS_SPI_CS_FIN: J_power_board_spacer_power_board_compan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.42, P_power_board_spacer_wakeup_board_power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.41
SYS_SPI_MISO: J_power_board_spacer_power_board_compan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.43, P_power_board_spacer_wakeup_board_power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.42
SYS_SPI_MOSI: J_power_board_spacer_power_board_compan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.44, P_power_board_spacer_wakeup_board_power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.43
SYS_SPI_SCLK: J_power_board_spacer_power_board_compan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.45, P_power_board_spacer_wakeup_board_power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.44
TMP1_ALERT: J_power_board_spacer_power_board_compan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.46, R_TMP1_ALERT_PU.2, U_TMP1.3
USBWK_GATE: P_power_board_spacer_wakeup_board_power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.45, Q_USB_WAKE.1, R_USBWK_G.2, R_USBWK_PD.1
USB_OR_EN: Q_USBOR_DRV.1, R_USBOR_USB_H.2, R_USBOR_USB_L.1
USB_OR_G: Q_USB_OR.3, R_USBOR_H.2, R_USBOR_L.1
USB_OR_GD: Q_USBOR_DRV.3, R_USBOR_L.2
USB_VBUS: C_USB_VBUS_1.1, C_USB_VBUS_2.1, C_USB_VBUS_3.1, C_USB_VBUS_4.1, C_USB_VBUS_5.1, J_power_board_spacer_power_board_compan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.47, Q_USB_OR.1, Q_USB_OR.2, Q_USB_OR.5, Q_USB_OR.6, R_ISO_USB_H.1, R_USBOR_USB_H.1, R_USBWK_G.1
WBA_BOOT0: J_power_board_spacer_power_board_compan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.48, P_power_board_spacer_wakeup_board_power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.46
WBA_HCI_IRQ: J_power_board_spacer_power_board_compan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.49, P_power_board_spacer_wakeup_board_power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.47
WBA_HCI_MISO: J_power_board_spacer_power_board_compan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.50, P_power_board_spacer_wakeup_board_power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.48
WBA_HCI_MOSI: J_power_board_spacer_power_board_compan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.51, P_power_board_spacer_wakeup_board_power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.49
WBA_HCI_NSS: J_power_board_spacer_power_board_compan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.52, P_power_board_spacer_wakeup_board_power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.50
WBA_HCI_SCK: J_power_board_spacer_power_board_compan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.53, P_power_board_spacer_wakeup_board_power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.51
WBA_RST_CMD: J_power_board_spacer_power_board_compan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.54, P_power_board_spacer_wakeup_board_power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.52
WBA_UART_RX: J_power_board_spacer_power_board_compan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.55, P_power_board_spacer_wakeup_board_power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.53
WBA_UART_TX: J_power_board_spacer_power_board_compan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.56, P_power_board_spacer_wakeup_board_power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.54
